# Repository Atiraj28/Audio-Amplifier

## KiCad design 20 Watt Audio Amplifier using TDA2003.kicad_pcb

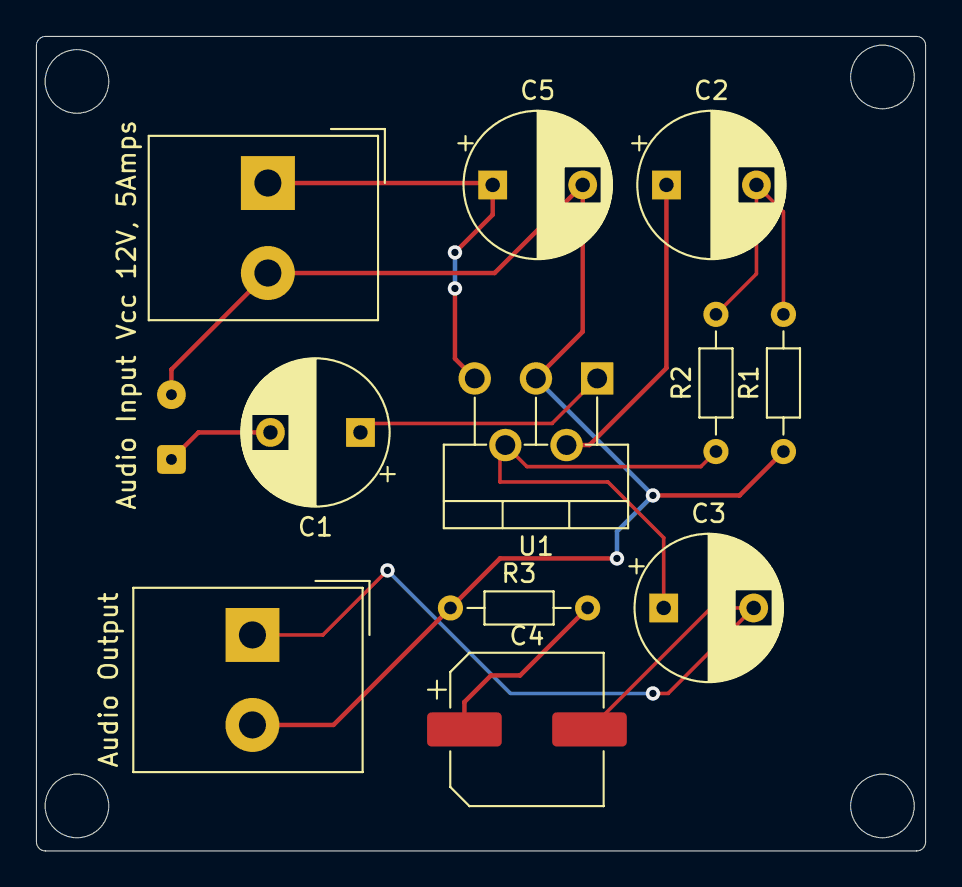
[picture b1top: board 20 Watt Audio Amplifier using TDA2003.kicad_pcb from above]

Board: 2 copper layers, 49.4 x 45.2 mm, 12 parts (0 on the bottom side), 3 nets.

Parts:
Audio Input: SolderWire-0.1sqmm_1x02_P3.6mm_D0.4mm_OD1mm
Audio Output: Altech_AK300_1x02_P5.00mm_45-Degree
C1, C2, C3, C5: CP_Radial_D8.0mm_P5.00mm
C4: CP_Elec_8x6.9
R1, R2, R3: R_Axial_DIN0204_L3.6mm_D1.6mm_P7.62mm_Horizontal
U1: TDA2003; TO-220-5_P3.4x3.7mm_StaggerOdd_Lead3.8mm_Vertical
Vcc 12V, 5Amps: Altech_AK300_1x02_P5.00mm_45-Degree

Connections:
Earth: Audio Input.2, Audio Output.2, C5.2, R1.1, R3.1, U1.3 (GND), Vcc 12V, 5Amps.2
unnamed: C3.1, U1.1 (+)
VCC: U1.5 (V+), Vcc 12V, 5Amps.1
